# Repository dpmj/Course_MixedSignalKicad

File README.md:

# Mixed-Signal Hardware Design with KiCad

My complete KiCAD project and report.

All my content is licensed under CERN-OHL-S (CERN Open Hardware Licence Version 2 - Strongly Reciprocal). 

Third-party desing elements included in this repository are subject to the copyright of their respective owners.

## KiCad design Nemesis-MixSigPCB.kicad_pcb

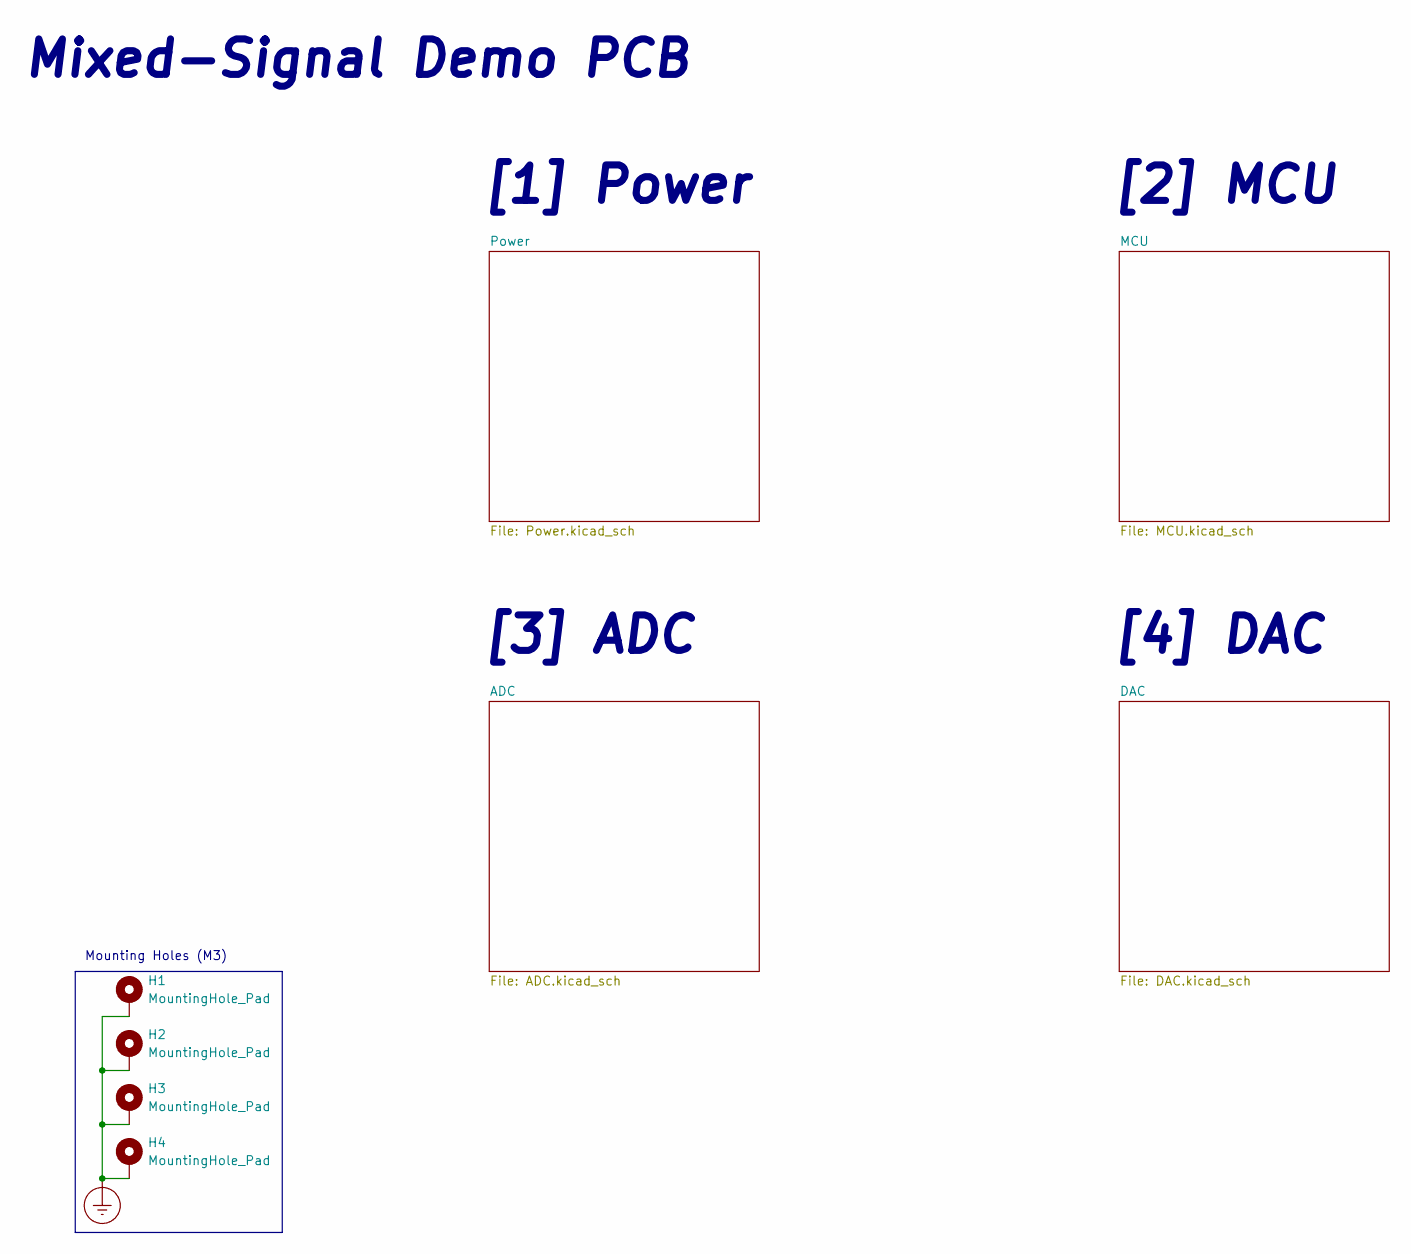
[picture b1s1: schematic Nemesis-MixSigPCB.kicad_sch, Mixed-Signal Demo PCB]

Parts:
H1, H2, H3, H4: MountingHole_Pad; MountingHole_3.2mm_M3_ISO7380_Pad

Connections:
Earth_Protective: H1.1, H2.1, H3.1, H4.1; also elsewhere on the board

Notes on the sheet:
[4] DAC
Mixed-Signal Demo PCB
[3] ADC
Mounting Holes (M3)
[2] MCU
[1] Power

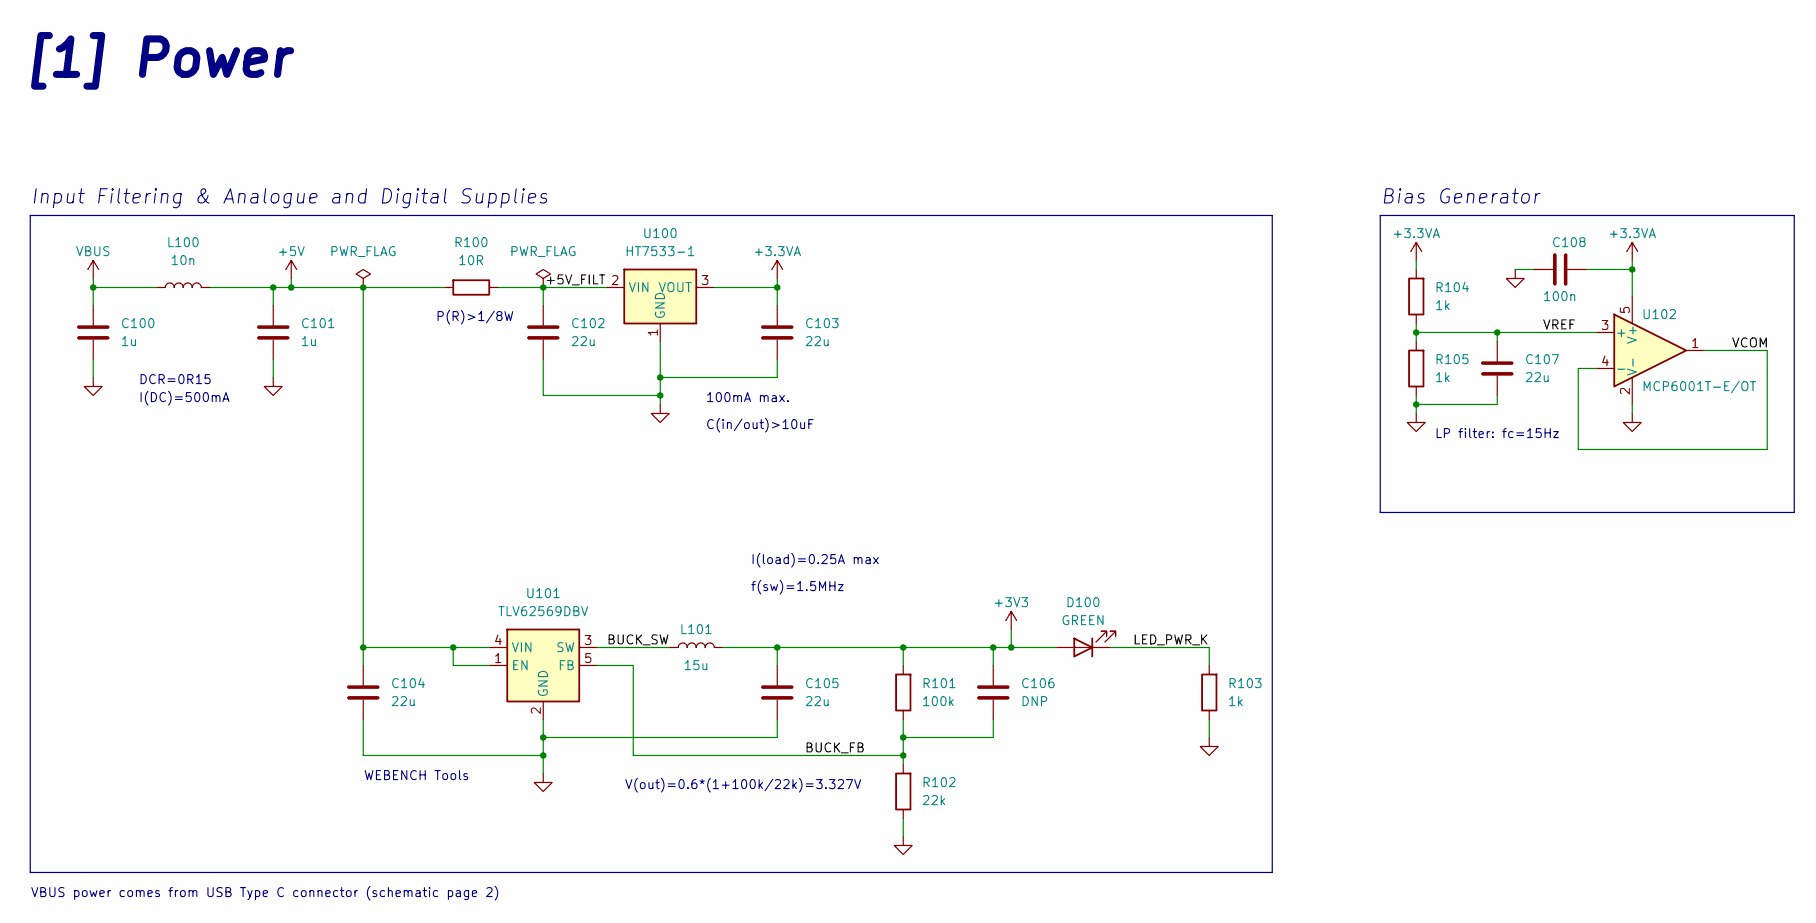
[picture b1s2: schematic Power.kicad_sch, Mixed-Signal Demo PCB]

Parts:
C100, C101: 1u; C_0603_1608Metric; Manufacturer Part Number C0603C105K8RACAUTO7411
C102, C103, C104, C105, C107: 22u; C_0805_2012Metric; Manufacturer Part Number CL21A226KPCLRNC
C106: DNP; C_0402_1005Metric
C108: 100n; C_0402_1005Metric; Manufacturer Part Number C0402C104K8RACAUTO
D100: GREEN; LED_0603_1608Metric
L100: 10n; L_0402_1005Metric; Manufacturer Part Number AISC-0402HP-10NJ-T
L101: 15u; MWSA0603S; Manufacturer Part Number MWSA0603S-150MT
R100: 10R; R_0805_2012Metric; Manufacturer Part Number CHP0805AJW-100ELF
R101: 100k; R_0402_1005Metric; Manufacturer Part Number ERJ-U02J104X
R102: 22k; R_0402_1005Metric; Manufacturer Part Number CR0402-JW-223GLF
R103, R104, R105: 1k; R_0402_1005Metric; Manufacturer Part Number CR0402-JW-102GLF
U100: HT7533-1; SOT-89-3; Manufacturer Part Number HT7533-1-SOT89
U101: TLV62569DBV; SOT-23-5; Manufacturer Part Number TLV62569DBVT
U102: MCP6001T-E/OT; SOT-23-5; Manufacturer Part Number MCP6001T-E/OT

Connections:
+3.3VA: C103.1, C108.1, R104.2, U100.3 (VOUT), U102.5 (V+); also elsewhere on the board
+3V3: C105.1, C106.1, D100.2 (A), L101.2, R101.2; also elsewhere on the board
+5V: C101.1, C104.1, L100.2, R100.2, U101.1 (EN), U101.4 (VIN); also elsewhere on the board
/Power/+5V_FILT: C102.1, R100.1, U100.2 (VIN)
/Power/BUCK_FB: C106.2, R101.1, R102.2, U101.5 (FB)
/Power/BUCK_SW: L101.1, U101.3 (SW)
/Power/LED_PWR_K: D100.1 (K), R103.2
/Power/VCOM: U102.1, U102.4 (-)
/Power/VREF: C107.1, R104.1, R105.2, U102.3 (+)
GND: C100.2, C101.2, C102.2, C103.2, C104.2, C105.2, C107.2, C108.2, R102.1, R103.1, R105.1, U100.1 (GND), U101.2 (GND), U102.2 (V-); also elsewhere on the board
VBUS: C100.1, L100.1; also elsewhere on the board

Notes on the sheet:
DCR=0R15
C(in/out)>10uF
V(out)=0.6*(1+100k/22k)=3.327V
I(DC)=500mA
Bias Generator
LP filter: fc=15Hz
100mA max.
f(sw)=1.5MHz
VBUS power comes from USB Type C connector (schematic page 2)
P(R)>1/8W
I(load)=0.25A max
Input Filtering & Analogue and Digital Supplies
[1] Power
WEBENCH Tools

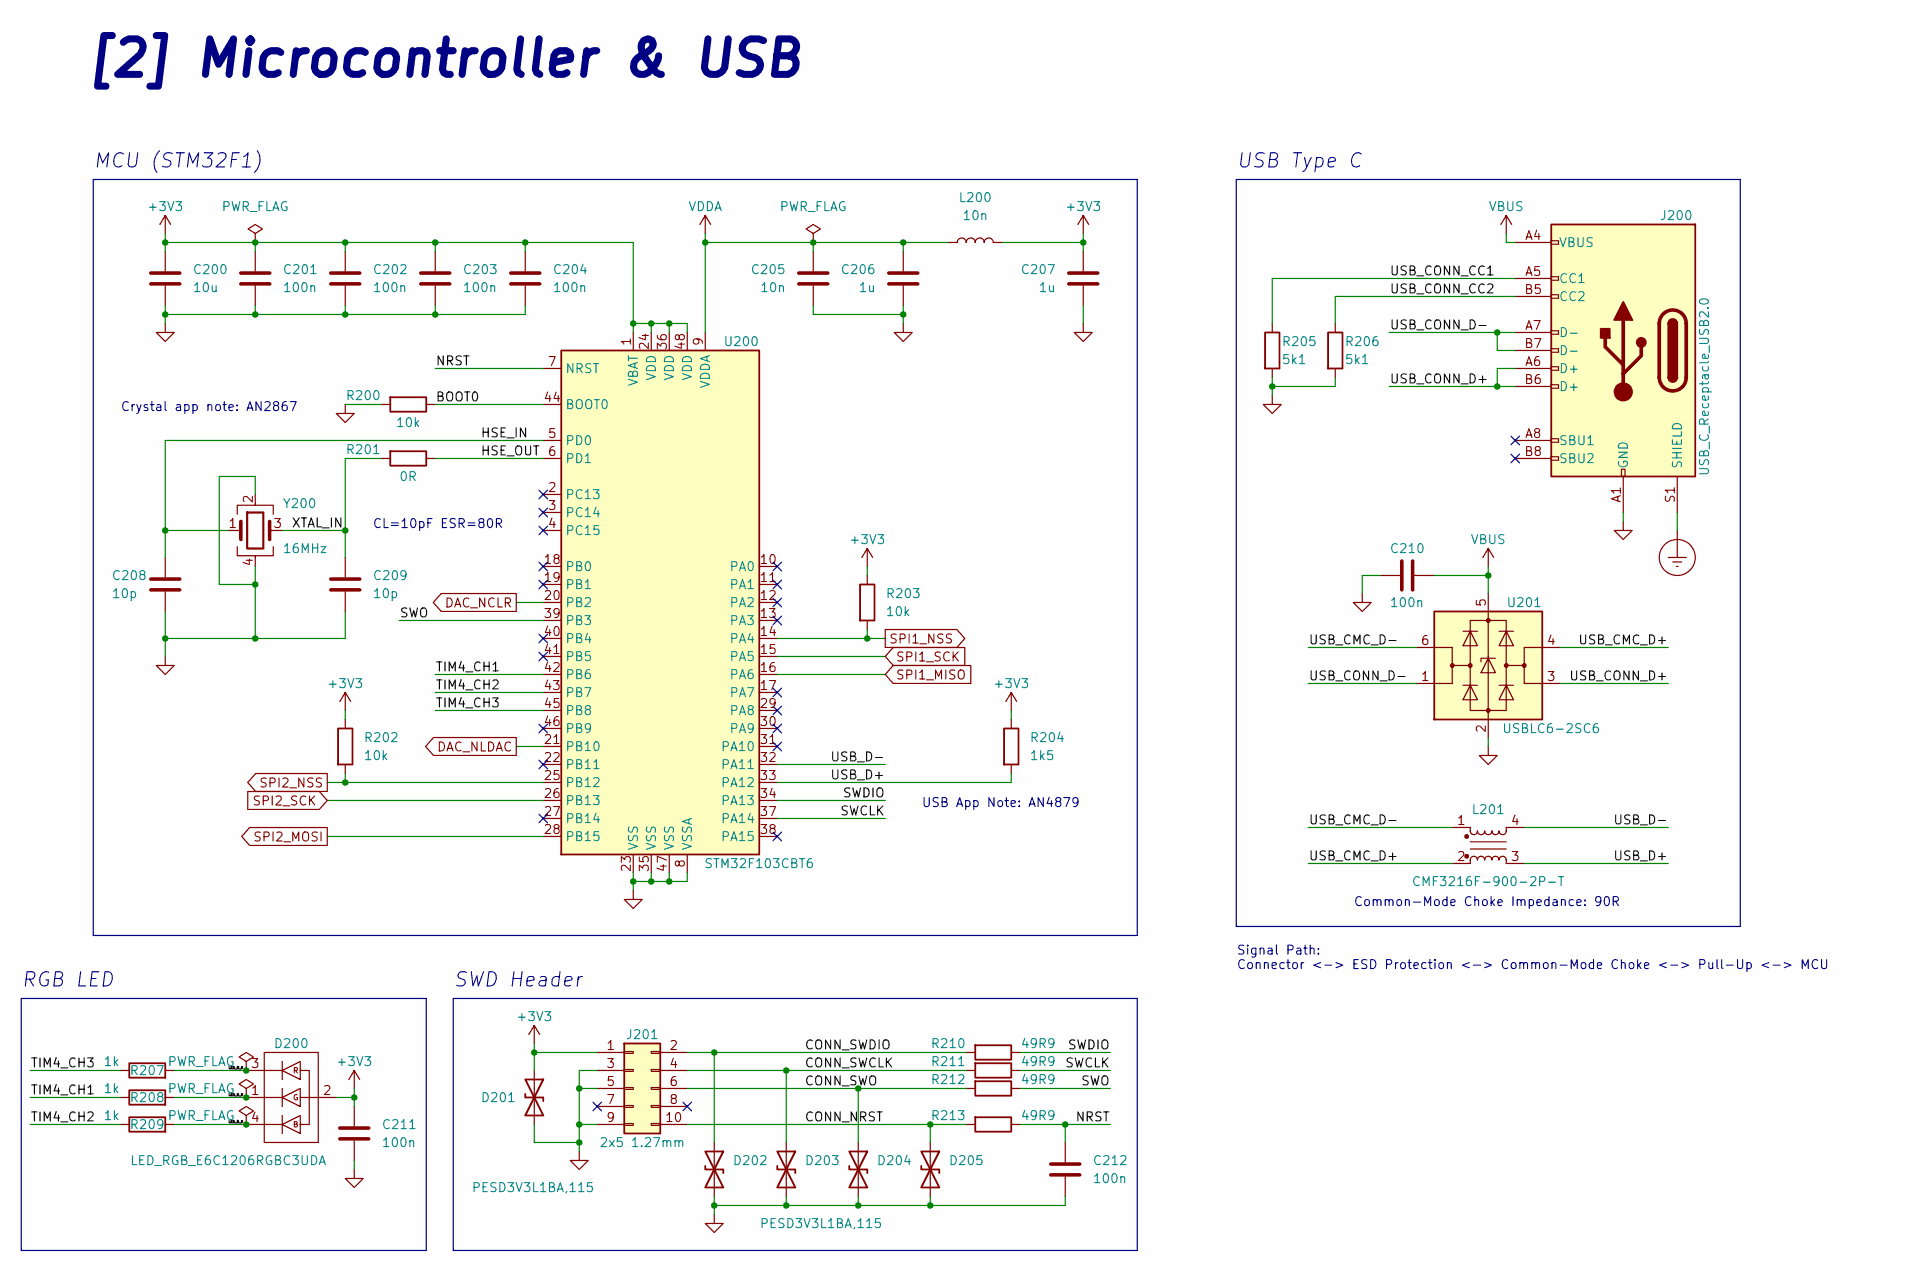
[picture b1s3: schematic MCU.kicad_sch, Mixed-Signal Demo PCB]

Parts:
C200: 10u; C_0603_1608Metric; Manufacturer Part Number CL10A106KQ8NNNL
C201, C202, C203, C204, C210, C211, C212: 100n; C_0402_1005Metric; Manufacturer Part Number C0402C104K8RACAUTO
C205: 10n; C_0402_1005Metric; Manufacturer Part Number C0402C103K4RACAUTO
C206, C207: 1u; C_0603_1608Metric; Manufacturer Part Number C0603C105K8RACAUTO7411
C208, C209: 10p; C_0402_1005Metric; Manufacturer Part Number GRT1555C1H100FA02D
D200: LED_RGB_E6C1206RGBC3UDA; LED_Cree-PLCC4_2x2mm_CW; Manufacturer Part Number E6C1206RGBC3UDA
D201, D202, D203, D204, D205: PESD3V3L1BA,115; D_SOD-323; Manufacturer Part Number PESD3V3L1BA,115
J200: USB_C_Receptacle_USB2.0; USB_C_Receptacle_HRO_TYPE-C-31-M-12; Manufacturer Part Number TYPE-C-31-M-12
J201: 2x5 1.27mm; PinHeader_2x05_P1.27mm_Vertical_SMD; Manufacturer Part Number M50-3600542R
L200: 10n; L_0402_1005Metric; Manufacturer Part Number AISC-0402HP-10NJ-T
L201: CMF3216F-900-2P-T; CMC-1206; Manufacturer Part Number CMF3216F-900-2P-T
R200, R202, R203: 10k; R_0402_1005Metric; Manufacturer Part Number ERJ-PA2J103X
R201: 0R; R_0402_1005Metric; Manufacturer Part Number CR0402AJ/-000GAS
R204: 1k5; R_0402_1005Metric; Manufacturer Part Number ERJ-PA2J152X
R205, R206: 5k1; R_0402_1005Metric; Manufacturer Part Number CR0402-JW-512GLF
R207, R208, R209: 1k; R_0402_1005Metric; Manufacturer Part Number CR0402-JW-102GLF
R210, R211, R212, R213: 49R9; R_0402_1005Metric; Manufacturer Part Number ERJ2RKD49R9X
U200: STM32F103CBT6; LQFP-48_7x7mm_P0.5mm; Manufacturer Part Number STM32F103CBT6
U201: USBLC6-2SC6; SOT-23-6; Manufacturer Part Number USBLC6-2SC6
Y200: 16MHz; Crystal_SMD_3225-4Pin_3.2x2.5mm; Manufacturer Part Number ECS-TXO-3225MV-160-TR

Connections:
+3V3: C200.1, C201.1, C202.1, C203.1, C204.1, C207.1, C211.1, D200.2, D201.1 (A1), J201.1, L200.2, R202.1, R203.1, R204.1, U200.1 (VBAT), U200.24 (VDD), U200.36 (VDD), U200.48 (VDD); also elsewhere on the board
/MCU/BOOT0: R200.1, U200.44 (BOOT0)
/MCU/CONN_NRST: D205.1 (A1), J201.10, R213.2
/MCU/CONN_SWCLK: D203.1 (A1), J201.4, R211.2
/MCU/CONN_SWDIO: D202.1 (A1), J201.2, R210.2
/MCU/CONN_SWO: D204.1 (A1), J201.6, R212.2
/MCU/HSE_IN: C208.1, U200.5 (PD0), Y200.1
/MCU/HSE_OUT: R201.1, U200.6 (PD1)
/MCU/LED_B_K: D200.4, R209.2
/MCU/LED_G_K: D200.1, R208.2
/MCU/LED_R_K: D200.3, R207.2
/MCU/NRST: C212.1, R213.1, U200.7 (NRST)
/MCU/SWCLK: R211.1, U200.37 (PA14)
/MCU/SWDIO: R210.1, U200.34 (PA13)
/MCU/SWO: R212.1, U200.39 (PB3)
/MCU/TIM4_CH1: R208.1, U200.42 (PB6)
/MCU/TIM4_CH2: R209.1, U200.43 (PB7)
/MCU/TIM4_CH3: R207.1, U200.45 (PB8)
/MCU/USB_CMC_D+: L201.2, U201.4 (I/O2)
/MCU/USB_CMC_D-: L201.1, U201.6 (I/O1)
/MCU/USB_CONN_CC1: J200.A5 (CC1), R205.1
/MCU/USB_CONN_CC2: J200.B5 (CC2), R206.1
/MCU/USB_CONN_D+: J200.A6 (D+), J200.B6 (D+), U201.3 (I/O2)
/MCU/USB_CONN_D-: J200.A7 (D-), J200.B7 (D-), U201.1 (I/O1)
/MCU/USB_D+: L201.3, R204.2, U200.33 (PA12)
/MCU/USB_D-: L201.4, U200.32 (PA11)
/MCU/XTAL_IN: C209.1, R201.2, Y200.3
DAC_NCLR: U200.20 (PB2); also elsewhere on the board
DAC_NLDAC: U200.21 (PB10); also elsewhere on the board
Earth_Protective: J200.S1 (SHIELD); also elsewhere on the board
GND: C200.2, C201.2, C202.2, C203.2, C204.2, C205.2, C206.2, C207.2, C208.2, C209.2, C210.2, C211.2, C212.2, D201.2 (A2), D202.2 (A2), D203.2 (A2), D204.2 (A2), D205.2 (A2), J200.A1 (GND), J200.A12 (GND), J200.B1 (GND), J200.B12 (GND), J201.3, J201.5, J201.9, R200.2, R205.2, R206.2, U200.8 (VSSA), U200.23 (VSS), U200.35 (VSS), U200.47 (VSS), U201.2 (GND), Y200.2, Y200.4; also elsewhere on the board
SPI1_MISO: U200.16 (PA6); also elsewhere on the board
SPI1_NSS: R203.2, U200.14 (PA4); also elsewhere on the board
SPI1_SCK: U200.15 (PA5); also elsewhere on the board
SPI2_MOSI: U200.28 (PB15); also elsewhere on the board
SPI2_NSS: R202.2, U200.25 (PB12); also elsewhere on the board
SPI2_SCK: U200.26 (PB13); also elsewhere on the board
VBUS: C210.1, J200.A4 (VBUS), J200.A9 (VBUS), J200.B4 (VBUS), J200.B9 (VBUS), U201.5 (VBUS); also elsewhere on the board
VDDA: C205.1, C206.1, L200.1, U200.9 (VDDA)

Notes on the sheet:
Signal Path: Connector <-> ESD Protection <-> Common-Mode Choke <-> Pull-Up <-> MCU
RGB LED
Crystal app note: AN2867
SWD Header
USB App Note: AN4879
Common-Mode Choke Impedance: 90R
[2] Microcontroller & USB
CL=10pF ESR=80R
MCU (STM32F1)
USB Type C

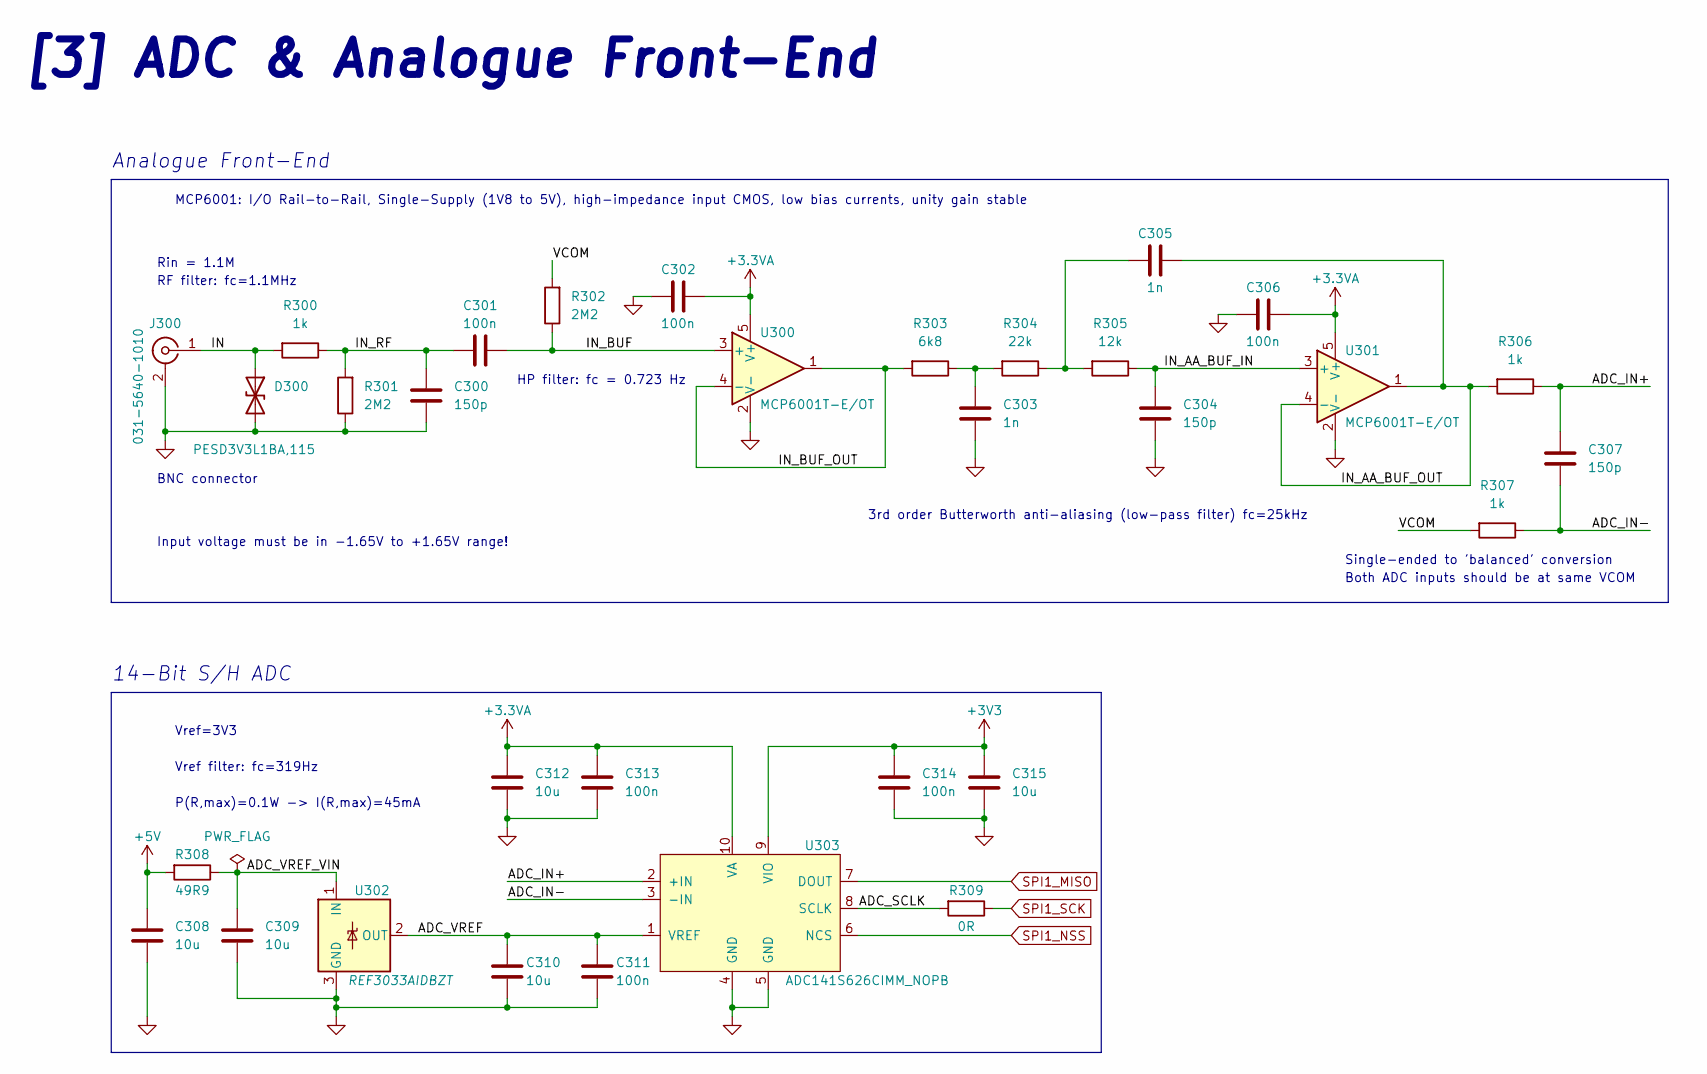
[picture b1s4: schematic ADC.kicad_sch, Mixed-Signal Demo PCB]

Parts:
C300, C304, C307: 150p; C_0402_1005Metric; Manufacturer Part Number 0402N151F100CT
C301, C302, C306, C311, C313, C314: 100n; C_0402_1005Metric; Manufacturer Part Number C0402C104K8RACAUTO
C303, C305: 1n; C_0402_1005Metric; Manufacturer Part Number AC0402JRNPO9BN102
C308, C309, C310, C312, C315: 10u; C_0603_1608Metric; Manufacturer Part Number CL10A106KQ8NNNL
D300: PESD3V3L1BA,115; D_SOD-323; Manufacturer Part Number PESD3V3L1BA,115
J300: 031-5640-1010; AMPHENOL-BNC-031-5640-1010; Manufacturer Part Number 031-5640
R300, R306, R307: 1k; R_0402_1005Metric; Manufacturer Part Number CR0402-JW-102GLF
R301, R302: 2M2; R_0402_1005Metric; Manufacturer Part Number ERJ-U02J205X
R303: 6k8; R_0402_1005Metric; Manufacturer Part Number ERJ-2GEJ682X
R304: 22k; R_0402_1005Metric; Manufacturer Part Number CR0402-JW-223GLF
R305: 12k; R_0402_1005Metric; Manufacturer Part Number CR0402-JW-123GLF
R308: 49R9; R_0402_1005Metric; Manufacturer Part Number ERJ2RKD49R9X
R309: 0R; R_0402_1005Metric; Manufacturer Part Number CR0402AJ/-000GAS
U300, U301: MCP6001T-E/OT; SOT-23-5; Manufacturer Part Number MCP6001T-E/OT
U302: REF3033AIDBZT; SOT-23; Manufacturer Part Number REF3033AIDBZT
U303: ADC141S626CIMM_NOPB; VSSOP-10; Manufacturer Part Number ADC141S626CIMM/NOPB

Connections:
+3.3VA: C302.1, C306.1, C312.1, C313.1, U300.5 (V+), U301.5 (V+), U303.10 (VA); also elsewhere on the board
+3V3: C314.1, C315.1, U303.9 (VIO); also elsewhere on the board
+5V: C308.1, R308.2; also elsewhere on the board
/ADC/ADC_IN+: C307.1, R306.1, U303.2 (+IN)
/ADC/ADC_IN-: C307.2, R307.1, U303.3 (-IN)
/ADC/ADC_SCLK: R309.2, U303.8 (SCLK)
/ADC/ADC_VREF: C310.1, C311.1, U302.2 (OUT), U303.1 (VREF)
/ADC/ADC_VREF_VIN: C309.1, R308.1, U302.1 (IN)
/ADC/IN: D300.1 (A1), J300.1 (In), R300.2
/ADC/IN_AA_BUF_IN: C304.1, R305.1, U301.3 (+)
/ADC/IN_AA_BUF_OUT: C305.2, R306.2, U301.1, U301.4 (-)
/ADC/IN_BUF: C301.1, R302.1, U300.3 (+)
/ADC/IN_BUF_OUT: R303.2, U300.1, U300.4 (-)
/ADC/IN_RF: C300.1, C301.2, R300.1, R301.2
/ADC/VCOM: R302.2, R307.2
GND: C300.2, C302.2, C303.2, C304.2, C306.2, C308.2, C309.2, C310.2, C311.2, C312.2, C313.2, C314.2, C315.2, D300.2 (A2), J300.2 (Ext), R301.1, U300.2 (V-), U301.2 (V-), U302.3 (GND), U303.4 (GND), U303.5 (GND); also elsewhere on the board
unnamed: C303.1, R303.1, R304.2
unnamed: C305.1, R304.1, R305.2
SPI1_MISO: U303.7 (DOUT); also elsewhere on the board
SPI1_NSS: U303.6 (NCS); also elsewhere on the board
SPI1_SCK: R309.1; also elsewhere on the board

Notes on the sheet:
HP filter: fc = 0.723 Hz
Both ADC inputs should be at same VCOM
BNC connector
Rin = 1.1M
14-Bit S/H ADC
Vref filter: fc=319Hz
Input voltage must be in -1.65V to +1.65V range!
Analogue Front-End
Single-ended to 'balanced' conversion
RF filter: fc=1.1MHz
3rd order Butterworth anti-aliasing (low-pass filter) fc=25kHz
MCP6001: I/O Rail-to-Rail, Single-Supply (1V8 to 5V), high-impedance input CMOS, low bias currents, unity gain stable
P(R,max)=0.1W -> I(R,max)=45mA
Vref=3V3
[3] ADC & Analogue Front-End

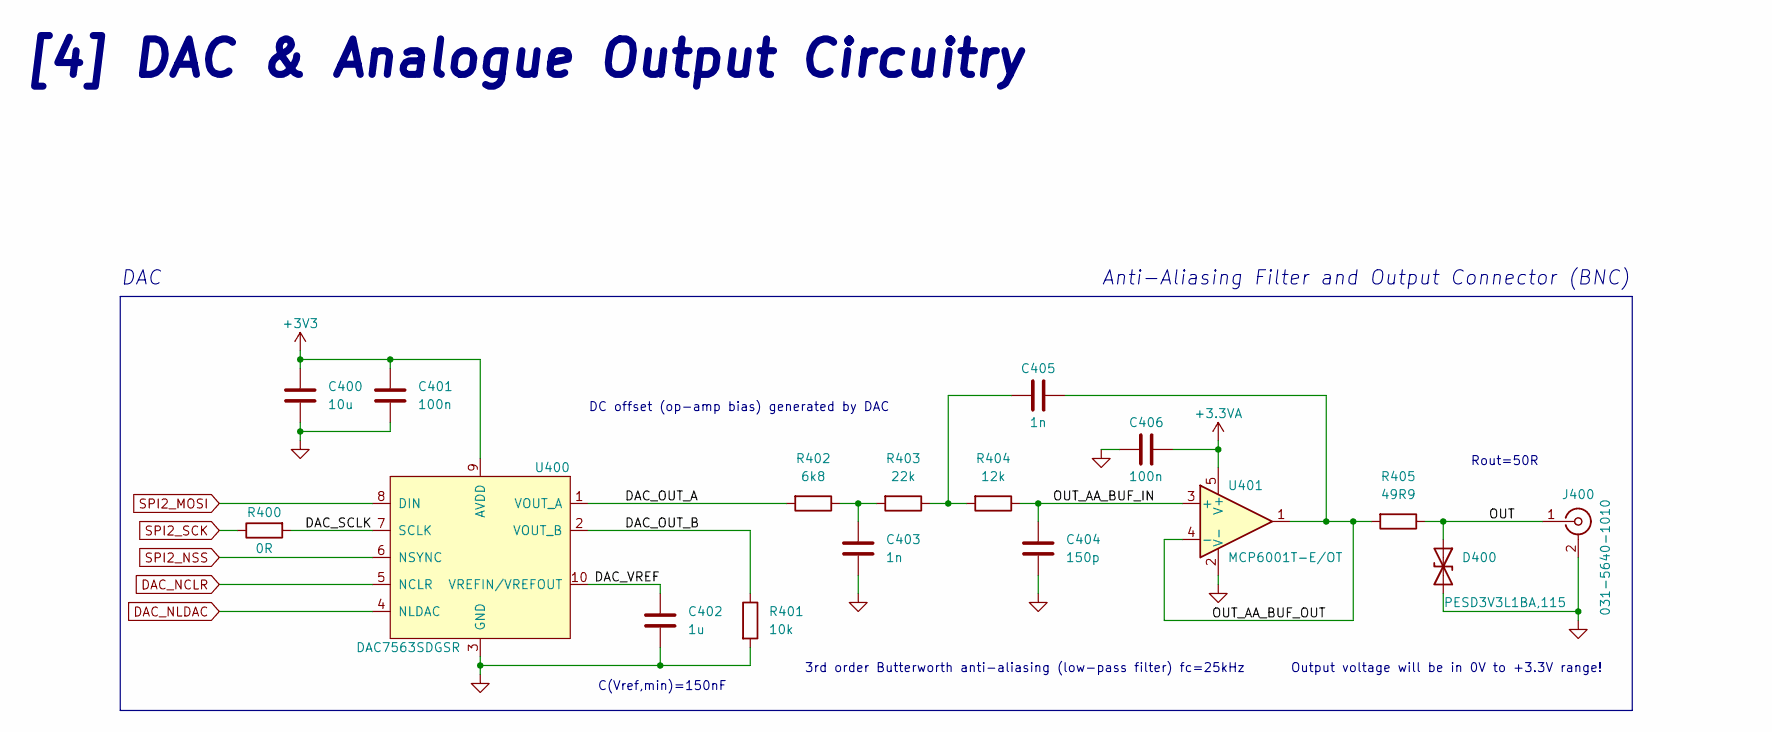
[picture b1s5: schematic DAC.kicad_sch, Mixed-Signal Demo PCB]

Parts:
C400: 10u; C_0603_1608Metric; Manufacturer Part Number CL10A106KQ8NNNL
C401, C406: 100n; C_0402_1005Metric; Manufacturer Part Number C0402C104K8RACAUTO
C402: 1u; C_0603_1608Metric; Manufacturer Part Number C0603C105K8RACAUTO7411
C403, C405: 1n; C_0402_1005Metric; Manufacturer Part Number AC0402JRNPO9BN102
C404: 150p; C_0402_1005Metric; Manufacturer Part Number 0402N151F100CT
D400: PESD3V3L1BA,115; D_SOD-323; Manufacturer Part Number PESD3V3L1BA,115
J400: 031-5640-1010; AMPHENOL-BNC-031-5640-1010; Manufacturer Part Number 031-5640
R400: 0R; R_0402_1005Metric; Manufacturer Part Number CR0402AJ/-000GAS
R401: 10k; R_0402_1005Metric; Manufacturer Part Number ERJ-PA2J103X
R402: 6k8; R_0402_1005Metric; Manufacturer Part Number ERJ-2GEJ682X
R403: 22k; R_0402_1005Metric; Manufacturer Part Number CR0402-JW-223GLF
R404: 12k; R_0402_1005Metric; Manufacturer Part Number CR0402-JW-123GLF
R405: 49R9; R_0402_1005Metric; Manufacturer Part Number ERJ2RKD49R9X
U400: DAC7563SDGSR; VSSOP-10; Manufacturer Part Number DAC7563SDGSR
U401: MCP6001T-E/OT; SOT-23-5; Manufacturer Part Number MCP6001T-E/OT

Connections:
+3.3VA: C406.1, U401.5 (V+); also elsewhere on the board
+3V3: C400.1, C401.1, U400.9 (AVDD); also elsewhere on the board
/DAC/DAC_OUT_A: R402.2, U400.1 (VOUT_A)
/DAC/DAC_OUT_B: R401.1, U400.2 (VOUT_B)
/DAC/DAC_SCLK: R400.2, U400.7 (SCLK)
/DAC/DAC_VREF: C402.1, U400.10 (VREFIN/VREFOUT)
/DAC/OUT: D400.1 (A1), J400.1 (In), R405.1
/DAC/OUT_AA_BUF_IN: C404.1, R404.1, U401.3 (+)
/DAC/OUT_AA_BUF_OUT: C405.2, R405.2, U401.1, U401.4 (-)
DAC_NCLR: U400.5 (NCLR); also elsewhere on the board
DAC_NLDAC: U400.4 (NLDAC); also elsewhere on the board
GND: C400.2, C401.2, C402.2, C403.2, C404.2, C406.2, D400.2 (A2), J400.2 (Ext), R401.2, U400.3 (GND), U401.2 (V-); also elsewhere on the board
unnamed: C403.1, R402.1, R403.2
unnamed: C405.1, R403.1, R404.2
SPI2_MOSI: U400.8 (DIN); also elsewhere on the board
SPI2_NSS: U400.6 (NSYNC); also elsewhere on the board
SPI2_SCK: R400.1; also elsewhere on the board

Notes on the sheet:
[4] DAC & Analogue Output Circuitry
Anti-Aliasing Filter and Output Connector (BNC)
Rout=50R
Output voltage will be in 0V to +3.3V range!
DAC
C(Vref,min)=150nF
3rd order Butterworth anti-aliasing (low-pass filter) fc=25kHz
DC offset (op-amp bias) generated by DAC

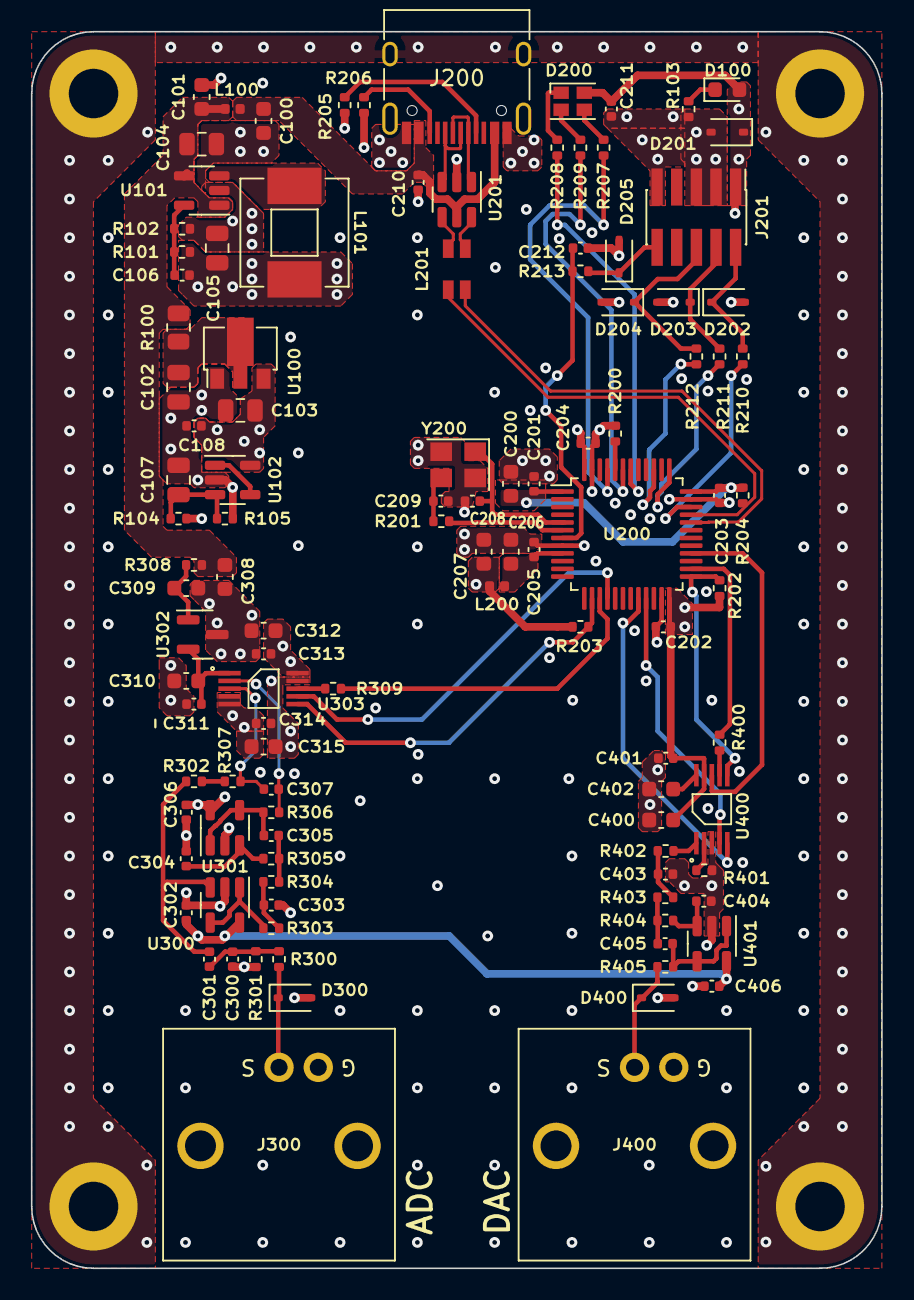
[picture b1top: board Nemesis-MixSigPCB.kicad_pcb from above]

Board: 4 copper layers, 55.0 x 80.0 mm, 114 parts (0 on the bottom side), 70 nets.

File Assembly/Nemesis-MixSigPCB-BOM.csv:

"Source:","/home/boi/Syncthing/Courses/2023-08 PhilsLab KiCad MixedSignal/MixSigCouse-KiCad-Files/Nemesis-MixSigPCB.kicad_sch"
"Date:","Sun 21 Jan 2024 09:14:26 PM CET"
"Tool:","Eeschema 7.0.10"
"Generator:","/usr/share/kicad/plugins/bom_csv_grouped_by_value_with_fp.py"
"Component Count:","114"
"Ref","Qnty","Value","Cmp name","Footprint","Description","Vendor","DNP","Manufacturer","Manufacturer Part Number"
"C100, C101, C206, C207, C402","5","1u","C","Capacitor_SMD:C_0603_1608Metric","Unpolarized capacitor","","KEMET","C0603C105K8RACAUTO7411",""
"C102, C103, C104, C105, C107","5","22u","C","Capacitor_SMD:C_0805_2012Metric","Unpolarized capacitor","","Samsung Electro-Mechanics","CL21A226KPCLRNC",""
"C106","1","DNP","C","Capacitor_SMD:C_0402_1005Metric","Unpolarized capacitor","","","",""
"C108, C201, C202, C203, C204, C210, C211, C212, C301, C302, C306, C311, C313, C314, C401, C406","16","100n","C","Capacitor_SMD:C_0402_1005Metric","Unpolarized capacitor","","KEMET","C0402C104K8RACAUTO",""
"C200, C308, C309, C310, C312, C315, C400","7","10u","C","Capacitor_SMD:C_0603_1608Metric","Unpolarized capacitor","","Samsung Electro-Mechanics","CL10A106KQ8NNNL",""
"C205","1","10n","C","Capacitor_SMD:C_0402_1005Metric","Unpolarized capacitor","","KEMET","C0402C103K4RACAUTO",""
"C208, C209","2","10p","C","Capacitor_SMD:C_0402_1005Metric","Unpolarized capacitor","","Murata Electronics","GRT1555C1H100FA02D",""
"C300, C304, C307, C404","4","150p","C","Capacitor_SMD:C_0402_1005Metric","Unpolarized capacitor","","Walsin ","0402N151F100CT ",""
"C303, C305, C403, C405","4","1n","C","Capacitor_SMD:C_0402_1005Metric","Unpolarized capacitor",""," YAGEO","AC0402JRNPO9BN102",""
"D100","1","GREEN","LED","LED_SMD:LED_0603_1608Metric","Light emitting diode","","","",""
"D200","1","LED_RGB_E6C1206RGBC3UDA","LED_RGB_E6C1206RGBC3UDA","LED_SMD:LED_Cree-PLCC4_2x2mm_CW","","","EKINGLUX","E6C1206RGBC3UDA",""
"D201, D202, D203, D204, D205, D300, D400","7","PESD3V3L1BA,115","D_TVS","Diode_SMD:D_SOD-323","Bidirectional transient-voltage-suppression diode","","Nexperia ","PESD3V3L1BA,115 ",""
"H1, H2, H3, H4","4","MountingHole_Pad","MountingHole_Pad","MountingHole:MountingHole_3.2mm_M3_ISO7380_Pad","Mounting Hole with connection","","","",""
"J200","1","USB_C_Receptacle_USB2.0","USB_C_Receptacle_USB2.0","Juan_Footprints_Lib:USB_C_Receptacle_HRO_TYPE-C-31-M-12","USB 2.0-only Type-C Receptacle connector","","Korean Hroparts Elec","TYPE-C-31-M-12",""
"J201","1","2x5 1.27mm","Conn_02x05_Odd_Even","Connector_PinHeader_1.27mm:PinHeader_2x05_P1.27mm_Vertical_SMD","Generic connector, double row, 02x05, odd/even pin numbering scheme (row 1 odd numbers, row 2 even numbers), script generated (kicad-library-utils/schlib/autogen/connector/)","","Harwin ","M50-3600542R ",""
"J300, J400","2","031-5640-1010","Conn_Coaxial","PhilsLab_Footprints_KiCad6:AMPHENOL-BNC-031-5640-1010","coaxial connector (BNC, SMA, SMB, SMC, Cinch/RCA, LEMO, ...)","","Amphenol RF ","031-5640",""
"L100, L200","2","10n","L","Inductor_SMD:L_0402_1005Metric","Inductor","","ABRACON ","AISC-0402HP-10NJ-T",""
"L101","1","15u","L","PhilsLab_Footprints_KiCad6:MWSA0603S","Inductor","","Shenzhen Sunlord Electronics","MWSA0603S-150MT",""
"L201","1","CMF3216F-900-2P-T","EMI_Filter_LL_1423","PhilsLab_Footprints_KiCad6:CMC-1206","","","HYHONGYEX","CMF3216F-900-2P-T",""
"R100","1","10R","R","Resistor_SMD:R_0805_2012Metric","Resistor","","Bourns","CHP0805AJW-100ELF",""
"R101","1","100k","R","Resistor_SMD:R_0402_1005Metric","Resistor","","Panasonic","ERJ-U02J104X",""
"R102, R304, R403","3","22k","R","Resistor_SMD:R_0402_1005Metric","Resistor","","Bourns","CR0402-JW-223GLF",""
"R103, R104, R105, R207, R208, R209, R300, R306, R307","9","1k","R","Resistor_SMD:R_0402_1005Metric","Resistor","","Bourns","CR0402-JW-102GLF",""
"R200, R202, R203, R401","4","10k","R","Resistor_SMD:R_0402_1005Metric","Resistor","","Panasonic","ERJ-PA2J103X",""
"R201, R309, R400","3","0R","R","Resistor_SMD:R_0402_1005Metric","Resistor","","Bourns","CR0402AJ/-000GAS",""
"R204","1","1k5","R","Resistor_SMD:R_0402_1005Metric","Resistor","","Panasonic","ERJ-PA2J152X",""
"R205, R206","2","5k1","R","Resistor_SMD:R_0402_1005Metric","Resistor","","Bourns","CR0402-JW-512GLF",""
"R210, R211, R212, R213, R308, R405","6","49R9","R","Resistor_SMD:R_0402_1005Metric","Resistor","","Panasonic","ERJ2RKD49R9X",""
"R301, R302","2","2M2","R","Resistor_SMD:R_0402_1005Metric","Resistor","","Panasonic","ERJ-U02J205X",""
"R303, R402","2","6k8","R","Resistor_SMD:R_0402_1005Metric","Resistor","","Panasonic","ERJ-2GEJ682X",""
"R305, R404","2","12k","R","Resistor_SMD:R_0402_1005Metric","Resistor","","Bourns","CR0402-JW-123GLF",""
"U100","1","HT7533-1","HT75xx-1-SOT89","Package_TO_SOT_SMD:SOT-89-3","100mA Low Dropout Voltage Regulator, Fixed Output, SOT89","","Holtek","HT7533-1-SOT89",""
"U101","1","TLV62569DBV","TLV62569DBV","Package_TO_SOT_SMD:SOT-23-5","High Efficiency Synchronous Buck Converter, Adjustable Output 0.6V-5.5V, 2A, SOT-23-5","","Texas Instruments ","TLV62569DBVT",""
"U102, U300, U301, U401","4","MCP6001T-E/OT","MCP6001-OT","Package_TO_SOT_SMD:SOT-23-5","1MHz, Low-Power Op Amp, SOT-23-5","","Microchip Technology ","MCP6001T-E/OT ",""
"U200","1","STM32F103CBT6","STM32F103CBTx","Package_QFP:LQFP-48_7x7mm_P0.5mm","ARM Cortex-M3 MCU, 128KB flash, 20KB RAM, 72MHz, 2-3.6V, 37 GPIO, LQFP-48","","STMicroelectronics","STM32F103CBT6",""
"U201","1","USBLC6-2SC6","USBLC6-2SC6","Package_TO_SOT_SMD:SOT-23-6","Very low capacitance ESD protection diode, 2 data-line, SOT-23-6","","STMicroelectronics ","USBLC6-2SC6",""
"U302","1","REF3033AIDBZT","REF3033","Package_TO_SOT_SMD:SOT-23","3.3V 50-ppm/°C Max, 50-μA, CMOS Voltage Reference, SOT-23-3","","Texas Instruments ","REF3033AIDBZT ",""
"U303","1","ADC141S626CIMM_NOPB","ADC141S626CIMM_NOPB","PhilsLab_Footprints_KiCad6:VSSOP-10","","","Texas Instruments ","ADC141S626CIMM/NOPB ",""
"U400","1","DAC7563SDGSR","DAC7563SDGSR","PhilsLab_Footprints_KiCad6:VSSOP-10","","","Texas Instruments ","DAC7563SDGSR",""
"Y200","1","16MHz","Crystal_GND24","Crystal:Crystal_SMD_3225-4Pin_3.2x2.5mm","Four pin crystal, GND on pins 2 and 4","","ECS ","ECS-TXO-3225MV-160-TR",""

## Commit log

2024-02-08 Course complete - upload to GitHub
2024-02-08 Added readme and report
2025-09-24 Rename cern_ohl_s_v2.txt to LICENSE
